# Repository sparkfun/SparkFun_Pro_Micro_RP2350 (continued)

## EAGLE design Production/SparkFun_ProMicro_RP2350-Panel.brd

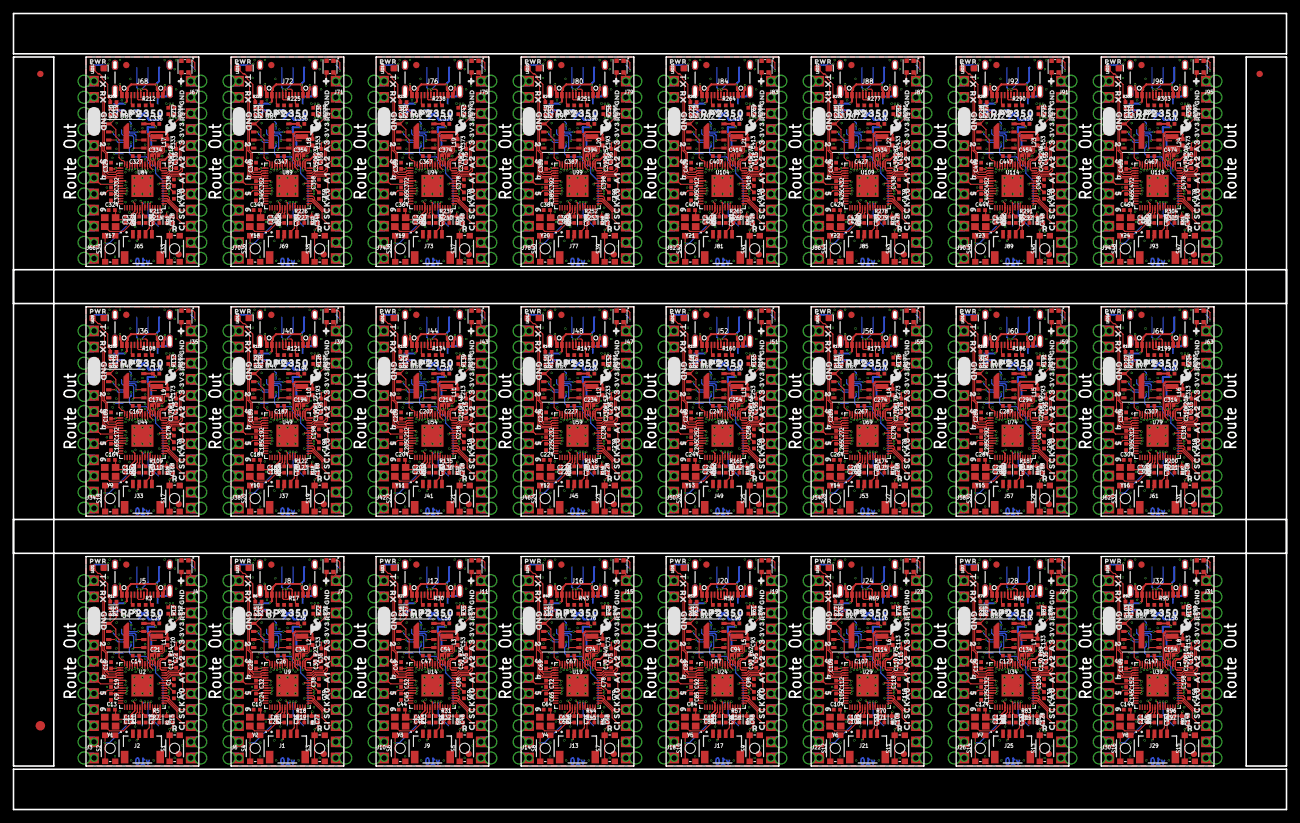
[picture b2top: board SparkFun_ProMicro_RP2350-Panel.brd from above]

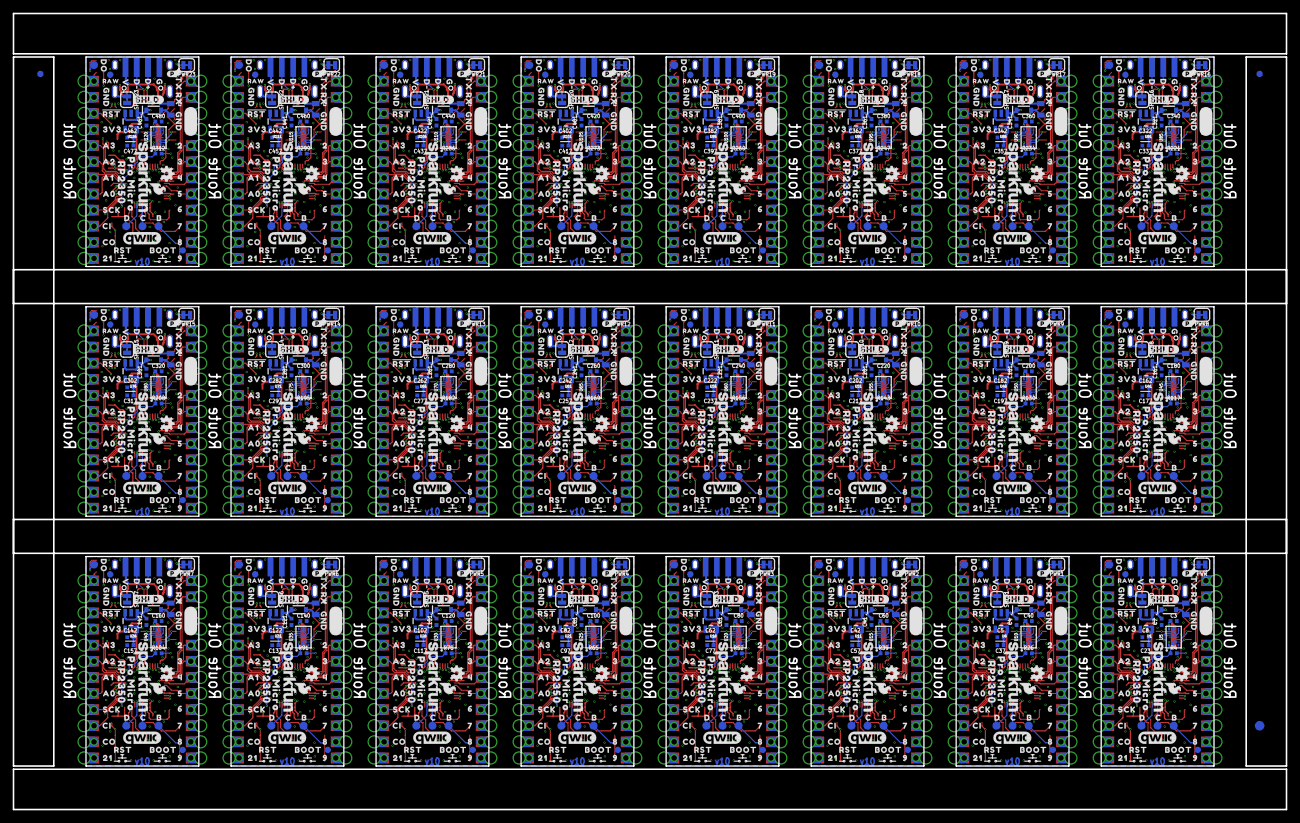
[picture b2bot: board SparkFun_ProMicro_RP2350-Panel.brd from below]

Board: 4 copper layers, 200.7 x 125.5 mm, 2934 parts (1395 on the bottom side), 1272 nets.

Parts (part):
C1, C2, C3, C9, C12, C14, C15, C16, C17, C18, C19, C24, C25, C26, C27, C28, C29, C30, C31, C32, C36, C38, C39, C40, C45, C46, C47, C48, C49, C50, C51, C52, C56, C58, C59, C60, C65, C66, C67, C68, C69, C70, C71, C72, C76, C78, C79, C80, C85, C86, C87, C88, C89, C90, C91, C92, C96, C98, C99, C100, C105, C106, C107, C108, C109, C110, C111, C112, C116, C118, C119, C120, C125, C126, C127, C128, C129, C130, C131, C132, C136, C138, C139, C140, C145, C146, C147, C148, C149, C150, C151, C152, C156, C158, C159, C160, C165, C166, C167, C168, C169, C170, C171, C172, C176, C178, C179, C180, C185, C186, C187, C188, C189, C190, C191, C192, C196, C198, C199, C200, C205, C206, C207, C208, C209, C210, C211, C212, C216, C218, C219, C220, C225, C226, C227, C228, C229, C230, C231, C232, C236, C238, C239, C240, C245, C246, C247, C248, C249, C250, C251, C252, C256, C258, C259, C260, C265, C266, C267, C268, C269, C270, C271, C272, C276, C278, C279, C280, C285, C286, C287, C288, C289, C290, C291, C292, C296, C298, C299, C300, C305, C306, C307, C308, C309, C310, C311, C312, C316, C318, C319, C320, C325, C326, C327, C328, C329, C330, C331, C332, C336, C338, C339, C340, C345, C346, C347, C348, C349, C350, C351, C352, C356, C358, C359, C360, C365, C366, C367, C368, C369, C370, C371, C372, C376, C378, C379, C380, C385, C386, C387, C388, C389, C390, C391, C392, C396, C398, C399, C400, C405, C406, C407, C408, C409, C410, C411, C412, C416, C418, C419, C420, C425, C426, C427, C428, C429, C430, C431, C432, C436, C438, C439, C440, C445, C446, C447, C448, C449, C450, C451, C452, C456, C458, C459, C460, C465, C466, C467, C468, C469, C470, C471, C472, C476, C478, C479, C480: 0.1uF; 0402-TIGHT
C4, C5, C7, C8, C20, C21, C33, C34, C41, C42, C53, C54, C61, C62, C73, C74, C81, C82, C93, C94, C101, C102, C113, C114, C121, C122, C133, C134, C141, C142, C153, C154, C161, C162, C173, C174, C181, C182, C193, C194, C201, C202, C213, C214, C221, C222, C233, C234, C241, C242, C253, C254, C261, C262, C273, C274, C281, C282, C293, C294, C301, C302, C313, C314, C321, C322, C333, C334, C341, C342, C353, C354, C361, C362, C373, C374, C381, C382, C393, C394, C401, C402, C413, C414, C421, C422, C433, C434, C441, C442, C453, C454, C461, C462, C473, C474: 10uF; 0402-TIGHT
C6, C10, C11, C13, C43, C44, C63, C64, C83, C84, C103, C104, C123, C124, C143, C144, C163, C164, C183, C184, C203, C204, C223, C224, C243, C244, C263, C264, C283, C284, C303, C304, C323, C324, C343, C344, C363, C364, C383, C384, C403, C404, C423, C424, C443, C444, C463, C464: 15pF; 0402-TIGHT
C22, C23, C35, C37, C55, C57, C75, C77, C95, C97, C115, C117, C135, C137, C155, C157, C175, C177, C195, C197, C215, C217, C235, C237, C255, C257, C275, C277, C295, C297, C315, C317, C335, C337, C355, C357, C375, C377, C395, C397, C415, C417, C435, C437, C455, C457, C475, C477: 2.2uF; 0402-TIGHT
D1, D2, D3, D4, D5, D6, D7, D8, D9, D10, D11, D12, D13, D14, D15, D16, D17, D18, D19, D20, D21, D22, D23, D24: 3A/10V/280mV; SOD-323
E$1, E$2, E$3, E$4: FIDUCIAL-1X2
E$5, E$6: FIDUCIAL-1.5X3
F1, F2, F3, F4, F5, F6, F7, F8, F9, F10, F11, F12, F13, F14, F15, F16, F17, F18, F19, F20, F21, F22, F23, F24: 6V 0.5A; 0805
J1, J2, J9, J13, J17, J21, J25, J29, J33, J37, J41, J45, J49, J53, J57, J61, J65, J69, J73, J77, J81, J85, J89, J93: QWIIC_RIGHT_ANGLE; JST04_1MM_RA
J3, J4, J6, J7, J10, J11, J14, J15, J18, J19, J22, J23, J26, J27, J30, J31, J34, J35, J38, J39, J42, J43, J46, J47, J50, J51, J54, J55, J58, J59, J62, J63, J66, J67, J70, J71, J74, J75, J78, J79, J82, J83, J86, J87, J90, J91, J94, J95: 1X12_CASTELLATED
J5, J8, J12, J16, J20, J24, J28, J32, J36, J40, J44, J48, J52, J56, J60, J64, J68, J72, J76, J80, J84, J88, J92, J96: USB Female Type C Connector; USB-C-16P_4LAYER-PADS
JP1, JP2, JP3, JP4, JP5, JP6, JP8, JP9, JP10, JP11, JP13, JP15, JP16, JP17, JP19, JP20, JP21, JP22, JP24, JP25, JP26, JP27, JP29, JP30, JP31, JP32, JP34, JP35, JP36, JP37, JP39, JP40, JP41, JP42, JP44, JP45, JP46, JP47, JP49, JP50, JP51, JP52, JP54, JP55, JP56, JP57, JP59, JP60, JP61, JP62, JP64, JP65, JP66, JP67, JP69, JP70, JP71, JP72, JP74, JP75, JP76, JP77, JP79, JP80, JP81, JP82, JP84, JP85, JP86, JP87, JP89, JP90, JP91, JP92, JP94, JP95, JP96, JP97, JP99, JP100, JP101, JP102, JP104, JP105, JP106, JP107, JP109, JP110, JP111, JP112, JP114, JP115, JP116, JP117, JP119, JP120: FIDUCIAL1X2; FIDUCIAL-1X2
JP7, JP12, JP14, JP18, JP23, JP28, JP33, JP38, JP43, JP48, JP53, JP58, JP63, JP68, JP73, JP78, JP83, JP88, JP93, JP98, JP103, JP108, JP113, JP118: USB_SOLDER_PADS; USB-SOLDER-PADS
L1, L2, L3, L4, L5, L6, L7, L8, L9, L10, L11, L12, L13, L14, L15, L16, L17, L18, L19, L20, L21, L22, L23, L24: 4.7μH; 1008(2520)
LED1, LED2, LED3, LED4, LED5, LED6, LED7, LED8, LED9, LED10, LED11, LED12, LED13, LED14, LED15, LED16, LED17, LED18, LED19, LED20, LED21, LED22, LED23, LED24: Red; LED-0603
LOGO1, LOGO2, LOGO7, LOGO10, LOGO13, LOGO16, LOGO19, LOGO22, LOGO25, LOGO28, LOGO31, LOGO34, LOGO37, LOGO40, LOGO43, LOGO46, LOGO49, LOGO52, LOGO55, LOGO58, LOGO61, LOGO64, LOGO67, LOGO70: SFE_LOGO_NAME_FLAME.1_INCH; SFE_LOGO_NAME_FLAME_.1
LOGO3, LOGO5, LOGO8, LOGO11, LOGO14, LOGO17, LOGO20, LOGO23, LOGO26, LOGO29, LOGO32, LOGO35, LOGO38, LOGO41, LOGO44, LOGO47, LOGO50, LOGO53, LOGO56, LOGO59, LOGO62, LOGO65, LOGO68, LOGO71: QWIIC_LOGO_6MM; QWIIC_6MM
LOGO4, LOGO6, LOGO9, LOGO12, LOGO15, LOGO18, LOGO21, LOGO24, LOGO27, LOGO30, LOGO33, LOGO36, LOGO39, LOGO42, LOGO45, LOGO48, LOGO51, LOGO54, LOGO57, LOGO60, LOGO63, LOGO66, LOGO69, LOGO72: SFE_LOGO_FLAME.1_INCH; SFE_LOGO_FLAME_.1
PWR, PWR1, PWR2, PWR3, PWR4, PWR5, PWR6, PWR7, PWR8, PWR9, PWR10, PWR11, PWR12, PWR13, PWR14, PWR15, PWR16, PWR17, PWR18, PWR19, PWR20, PWR21, PWR22, PWR23: JUMPER-SMT_2_NC_TRACE_SILK; SMT-JUMPER_2_NC_TRACE_SILK
R1, R3, R9, R17, R29, R30, R42, R43, R55, R56, R68, R69, R81, R82, R94, R95, R107, R108, R120, R121, R133, R134, R146, R147, R159, R160, R172, R173, R185, R186, R198, R199, R211, R212, R224, R225, R237, R238, R250, R251, R263, R264, R276, R277, R289, R290, R302, R303: 5.1k; 0402-TIGHT
R2, R4, R8, R16, R25, R26, R28, R38, R39, R41, R51, R52, R54, R64, R65, R67, R77, R78, R80, R90, R91, R93, R103, R104, R106, R116, R117, R119, R129, R130, R132, R142, R143, R145, R155, R156, R158, R168, R169, R171, R181, R182, R184, R194, R195, R197, R207, R208, R210, R220, R221, R223, R233, R234, R236, R246, R247, R249, R259, R260, R262, R272, R273, R275, R285, R286, R288, R298, R299, R301, R311, R312: 10k; 0402-TIGHT
R5, R7, R18, R19, R31, R32, R44, R45, R57, R58, R70, R71, R83, R84, R96, R97, R109, R110, R122, R123, R135, R136, R148, R149, R161, R162, R174, R175, R187, R188, R200, R201, R213, R214, R226, R227, R239, R240, R252, R253, R265, R266, R278, R279, R291, R292, R304, R305: 2.2k; 0402-TIGHT
R6, R11, R27, R40, R53, R66, R79, R92, R105, R118, R131, R144, R157, R170, R183, R196, R209, R222, R235, R248, R261, R274, R287, R300: 4.7k; 0402-TIGHT
R10, R15, R20, R24, R33, R37, R46, R50, R59, R63, R72, R76, R85, R89, R98, R102, R111, R115, R124, R128, R137, R141, R150, R154, R163, R167, R176, R180, R189, R193, R202, R206, R215, R219, R228, R232, R241, R245, R254, R258, R267, R271, R280, R284, R293, R297, R306, R310: 1k; 0402-TIGHT
R12, R13, R21, R22, R34, R35, R47, R48, R60, R61, R73, R74, R86, R87, R99, R100, R112, R113, R125, R126, R138, R139, R151, R152, R164, R165, R177, R178, R190, R191, R203, R204, R216, R217, R229, R230, R242, R243, R255, R256, R268, R269, R281, R282, R294, R295, R307, R308: 27; 0402-TIGHT
R14, R23, R36, R49, R62, R75, R88, R101, R114, R127, R140, R153, R166, R179, R192, R205, R218, R231, R244, R257, R270, R283, R296, R309: 10Ω; 0402-TIGHT
S1, S3, S5, S7, S9, S11, S13, S15, S17, S19, S21, S23, S25, S27, S29, S31, S33, S35, S37, S39, S41, S43, S45, S47: Reset; TACTILE_SWITCH_SMD_4.6X2.8MM
S2, S4, S6, S8, S10, S12, S14, S16, S18, S20, S22, S24, S26, S28, S30, S32, S34, S36, S38, S40, S42, S44, S46, S48: Boot; TACTILE_SWITCH_SMD_4.6X2.8MM
SHLD, SHLD1, SHLD2, SHLD3, SHLD4, SHLD5, SHLD6, SHLD7, SHLD8, SHLD9, SHLD10, SHLD11, SHLD12, SHLD13, SHLD14, SHLD15, SHLD16, SHLD17, SHLD18, SHLD19, SHLD20, SHLD21, SHLD22, SHLD23: JUMPER-SMT_2_NC_TRACE_SILK; SMT-JUMPER_2_NC_TRACE_SILK
TP1, TP2, TP3, TP4, TP5, TP6, TP7, TP8, TP9, TP10, TP11, TP12, TP13, TP14, TP15, TP16, TP17, TP18, TP19, TP20, TP21, TP22, TP23, TP24, TP25, TP26, TP27, TP28, TP29, TP30, TP31, TP32, TP33, TP34, TP35, TP36, TP37, TP38, TP39, TP40, TP41, TP42, TP43, TP44, TP45, TP46, TP47, TP48, TP49, TP50, TP51, TP52, TP53, TP54, TP55, TP56, TP57, TP58, TP59, TP60, TP61, TP62, TP63, TP64, TP65, TP66, TP67, TP68, TP69, TP70, TP71, TP72, TP73, TP74, TP75, TP76, TP77, TP78, TP79, TP80, TP81, TP82, TP83, TP84, TP85, TP86, TP87, TP88, TP89, TP90, TP91, TP92, TP93, TP94, TP95, TP96: TEST-POINT3X5; PAD.03X.05
U1, U6, U11, U16, U21, U26, U31, U36, U41, U46, U51, U56, U61, U66, U71, U76, U81, U86, U91, U96, U101, U106, U111, U116: RT9080-33GJ5; SOT23-5
U2, U9, U14, U19, U24, U29, U34, U39, U44, U49, U54, U59, U64, U69, U74, U79, U84, U89, U94, U99, U104, U109, U114, U119: RP2350A
U3, U8, U13, U18, U23, U28, U33, U38, U43, U48, U53, U58, U63, U68, U73, U78, U83, U88, U93, U98, U103, U108, U113, U118: WS2812_2020; WS2812-2020
U4, U7, U12, U17, U22, U27, U32, U37, U42, U47, U52, U57, U62, U67, U72, U77, U82, U87, U92, U97, U102, U107, U112, U117: W25QXX128MBIT; WSON-8-6X5-SKINNY_CENTERPAD
U5, U10, U15, U20, U25, U30, U35, U40, U45, U50, U55, U60, U65, U70, U75, U80, U85, U90, U95, U100, U105, U110, U115, U120: APS6404L-3SQR-ZR
U$1, U$11, U$47, U$85, U$120, U$144, U$179, U$203, U$238, U$262, U$297, U$321, U$356, U$380, U$415, U$439, U$474, U$498, U$533, U$557, U$592, U$616, U$651, U$675, U$710, U$734, U$769, U$793, U$828, U$852, U$887, U$911, U$946, U$970, U$1005, U$1029, U$1064, U$1088, U$1123, U$1147, U$1182, U$1206, U$1241, U$1265, U$1300, U$1324, U$1359, U$1383: A00
U$2, U$79, U$138, U$197, U$256, U$315, U$374, U$433, U$492, U$551, U$610, U$669, U$728, U$787, U$846, U$905, U$964, U$1023, U$1082, U$1141, U$1200, U$1259, U$1318, U$1377: GND_0
U$3, U$46, U$119, U$178, U$237, U$296, U$355, U$414, U$473, U$532, U$591, U$650, U$709, U$768, U$827, U$886, U$945, U$1004, U$1063, U$1122, U$1181, U$1240, U$1299, U$1358: OSHW-LOGOMINI; OSHW-LOGO-MINI
U$4, U$108, U$167, U$226, U$285, U$344, U$403, U$462, U$521, U$580, U$639, U$698, U$757, U$816, U$875, U$934, U$993, U$1052, U$1111, U$1170, U$1229, U$1288, U$1347, U$1406: PRO_MICRO0
U$5, U$107, U$166, U$225, U$284, U$343, U$402, U$461, U$520, U$579, U$638, U$697, U$756, U$815, U$874, U$933, U$992, U$1051, U$1110, U$1169, U$1228, U$1287, U$1346, U$1405: #0
U$6, U$80, U$139, U$198, U$257, U$316, U$375, U$434, U$493, U$552, U$611, U$670, U$729, U$788, U$847, U$906, U$965, U$1024, U$1083, U$1142, U$1201, U$1260, U$1319, U$1378: 70
U$7, U$81, U$140, U$199, U$258, U$317, U$376, U$435, U$494, U$553, U$612, U$671, U$730, U$789, U$848, U$907, U$966, U$1025, U$1084, U$1143, U$1202, U$1261, U$1320, U$1379: 81
U$8, U$82, U$141, U$200, U$259, U$318, U$377, U$436, U$495, U$554, U$613, U$672, U$731, U$790, U$849, U$908, U$967, U$1026, U$1085, U$1144, U$1203, U$1262, U$1321, U$1380: 92
U$9, U$51, U$64, U$83, U$124, U$142, U$183, U$201, U$242, U$260, U$301, U$319, U$360, U$378, U$419, U$437, U$478, U$496, U$537, U$555, U$596, U$614, U$655, U$673, U$714, U$732, U$773, U$791, U$832, U$850, U$891, U$909, U$950, U$968, U$1009, U$1027, U$1068, U$1086, U$1127, U$1145, U$1186, U$1204, U$1245, U$1263, U$1304, U$1322, U$1363, U$1381: CI4
U$10, U$58, U$67, U$84, U$126, U$143, U$185, U$202, U$244, U$261, U$303, U$320, U$362, U$379, U$421, U$438, U$480, U$497, U$539, U$556, U$598, U$615, U$657, U$674, U$716, U$733, U$775, U$792, U$834, U$851, U$893, U$910, U$952, U$969, U$1011, U$1028, U$1070, U$1087, U$1129, U$1146, U$1188, U$1205, U$1247, U$1264, U$1306, U$1323, U$1365, U$1382: SCK3
U$12, U$20, U$48, U$86, U$121, U$145, U$180, U$204, U$239, U$263, U$298, U$322, U$357, U$381, U$416, U$440, U$475, U$499, U$534, U$558, U$593, U$617, U$652, U$676, U$711, U$735, U$770, U$794, U$829, U$853, U$888, U$912, U$947, U$971, U$1006, U$1030, U$1065, U$1089, U$1124, U$1148, U$1183, U$1207, U$1242, U$1266, U$1301, U$1325, U$1360, U$1384: A10
U$13, U$33, U$49, U$87, U$122, U$146, U$181, U$205, U$240, U$264, U$299, U$323, U$358, U$382, U$417, U$441, U$476, U$500, U$535, U$559, U$594, U$618, U$653, U$677, U$712, U$736, U$771, U$795, U$830, U$854, U$889, U$913, U$948, U$972, U$1007, U$1031, U$1066, U$1090, U$1125, U$1149, U$1184, U$1208, U$1243, U$1267, U$1302, U$1326, U$1361, U$1385: A21
U$14, U$39, U$50, U$88, U$123, U$147, U$182, U$206, U$241, U$265, U$300, U$324, U$359, U$383, U$418, U$442, U$477, U$501, U$536, U$560, U$595, U$619, U$654, U$678, U$713, U$737, U$772, U$796, U$831, U$855, U$890, U$914, U$949, U$973, U$1008, U$1032, U$1067, U$1091, U$1126, U$1150, U$1185, U$1209, U$1244, U$1268, U$1303, U$1327, U$1362, U$1386: A32
U$15, U$22, U$72, U$74, U$91, U$104, U$135, U$150, U$163, U$194, U$209, U$222, U$253, U$268, U$281, U$312, U$327, U$340, U$371, U$386, U$399, U$430, U$445, U$458, U$489, U$504, U$517, U$548, U$563, U$576, U$607, U$622, U$635, U$666, U$681, U$694, U$725, U$740, U$753, U$784, U$799, U$812, U$843, U$858, U$871, U$902, U$917, U$930, U$961, U$976, U$989, U$1020, U$1035, U$1048, U$1079, U$1094, U$1107, U$1138, U$1153, U$1166, U$1197, U$1212, U$1225, U$1256, U$1271, U$1284, U$1315, U$1330, U$1343, U$1374, U$1389, U$1402: GND2
U$16, U$103, U$162, U$221, U$280, U$339, U$398, U$457, U$516, U$575, U$634, U$693, U$752, U$811, U$870, U$929, U$988, U$1047, U$1106, U$1165, U$1224, U$1283, U$1342, U$1401: 3V3_0
U$17, U$105, U$164, U$223, U$282, U$341, U$400, U$459, U$518, U$577, U$636, U$695, U$754, U$813, U$872, U$931, U$990, U$1049, U$1108, U$1167, U$1226, U$1285, U$1344, U$1403: RAW0
U$18, U$109, U$168, U$227, U$286, U$345, U$404, U$463, U$522, U$581, U$640, U$699, U$758, U$817, U$876, U$935, U$994, U$1053, U$1112, U$1171, U$1230, U$1289, U$1348, U$1407: C0
U$19, U$76, U$78, U$89, U$137, U$148, U$196, U$207, U$255, U$266, U$314, U$325, U$373, U$384, U$432, U$443, U$491, U$502, U$550, U$561, U$609, U$620, U$668, U$679, U$727, U$738, U$786, U$797, U$845, U$856, U$904, U$915, U$963, U$974, U$1022, U$1033, U$1081, U$1092, U$1140, U$1151, U$1199, U$1210, U$1258, U$1269, U$1317, U$1328, U$1376, U$1387: TX0
U$21, U$75, U$77, U$90, U$136, U$149, U$195, U$208, U$254, U$267, U$313, U$326, U$372, U$385, U$431, U$444, U$490, U$503, U$549, U$562, U$608, U$621, U$667, U$680, U$726, U$739, U$785, U$798, U$844, U$857, U$903, U$916, U$962, U$975, U$1021, U$1034, U$1080, U$1093, U$1139, U$1152, U$1198, U$1211, U$1257, U$1270, U$1316, U$1329, U$1375, U$1388: RX1
U$23, U$53, U$59, U$92, U$127, U$151, U$186, U$210, U$245, U$269, U$304, U$328, U$363, U$387, U$422, U$446, U$481, U$505, U$540, U$564, U$599, U$623, U$658, U$682, U$717, U$741, U$776, U$800, U$835, U$859, U$894, U$918, U$953, U$977, U$1012, U$1036, U$1071, U$1095, U$1130, U$1154, U$1189, U$1213, U$1248, U$1272, U$1307, U$1331, U$1366, U$1390: 20
U$24, U$54, U$60, U$93, U$128, U$152, U$187, U$211, U$246, U$270, U$305, U$329, U$364, U$388, U$423, U$447, U$482, U$506, U$541, U$565, U$600, U$624, U$659, U$683, U$718, U$742, U$777, U$801, U$836, U$860, U$895, U$919, U$954, U$978, U$1013, U$1037, U$1072, U$1096, U$1131, U$1155, U$1190, U$1214, U$1249, U$1273, U$1308, U$1332, U$1367, U$1391: 31
U$25, U$55, U$61, U$94, U$129, U$153, U$188, U$212, U$247, U$271, U$306, U$330, U$365, U$389, U$424, U$448, U$483, U$507, U$542, U$566, U$601, U$625, U$660, U$684, U$719, U$743, U$778, U$802, U$837, U$861, U$896, U$920, U$955, U$979, U$1014, U$1038, U$1073, U$1097, U$1132, U$1156, U$1191, U$1215, U$1250, U$1274, U$1309, U$1333, U$1368, U$1392: 42
U$26, U$56, U$62, U$95, U$130, U$154, U$189, U$213, U$248, U$272, U$307, U$331, U$366, U$390, U$425, U$449, U$484, U$508, U$543, U$567, U$602, U$626, U$661, U$685, U$720, U$744, U$779, U$803, U$838, U$862, U$897, U$921, U$956, U$980, U$1015, U$1039, U$1074, U$1098, U$1133, U$1157, U$1192, U$1216, U$1251, U$1275, U$1310, U$1334, U$1369, U$1393: 53
U$27, U$57, U$63, U$96, U$131, U$155, U$190, U$214, U$249, U$273, U$308, U$332, U$367, U$391, U$426, U$450, U$485, U$509, U$544, U$568, U$603, U$627, U$662, U$686, U$721, U$745, U$780, U$804, U$839, U$863, U$898, U$922, U$957, U$981, U$1016, U$1040, U$1075, U$1099, U$1134, U$1158, U$1193, U$1217, U$1252, U$1276, U$1311, U$1335, U$1370, U$1394: 64
U$28, U$97, U$156, U$215, U$274, U$333, U$392, U$451, U$510, U$569, U$628, U$687, U$746, U$805, U$864, U$923, U$982, U$1041, U$1100, U$1159, U$1218, U$1277, U$1336, U$1395: D#1
U$29, U$98, U$157, U$216, U$275, U$334, U$393, U$452, U$511, U$570, U$629, U$688, U$747, U$806, U$865, U$924, U$983, U$1042, U$1101, U$1160, U$1219, U$1278, U$1337, U$1396: D#2
U$30, U$99, U$158, U$217, U$276, U$335, U$394, U$453, U$512, U$571, U$630, U$689, U$748, U$807, U$866, U$925, U$984, U$1043, U$1102, U$1161, U$1220, U$1279, U$1338, U$1397: G0
U$31, U$100, U$159, U$218, U$277, U$336, U$395, U$454, U$513, U$572, U$631, U$690, U$749, U$808, U$867, U$926, U$985, U$1044, U$1103, U$1162, U$1221, U$1280, U$1339, U$1398: V3
U$32, U$101, U$160, U$219, U$278, U$337, U$396, U$455, U$514, U$573, U$632, U$691, U$750, U$809, U$868, U$927, U$986, U$1045, U$1104, U$1163, U$1222, U$1281, U$1340, U$1399: 210
U$34, U$102, U$161, U$220, U$279, U$338, U$397, U$456, U$515, U$574, U$633, U$692, U$751, U$810, U$869, U$928, U$987, U$1046, U$1105, U$1164, U$1223, U$1282, U$1341, U$1400: #RST#0
U$35, U$110, U$169, U$228, U$287, U$346, U$405, U$464, U$523, U$582, U$641, U$700, U$759, U$818, U$877, U$936, U$995, U$1054, U$1113, U$1172, U$1231, U$1290, U$1349, U$1408: D1
U$36, U$115, U$174, U$233, U$292, U$351, U$410, U$469, U$528, U$587, U$646, U$705, U$764, U$823, U$882, U$941, U$1000, U$1059, U$1118, U$1177, U$1236, U$1295, U$1354, U$1413: #P#0
U$37, U$106, U$165, U$224, U$283, U$342, U$401, U$460, U$519, U$578, U$637, U$696, U$755, U$814, U$873, U$932, U$991, U$1050, U$1109, U$1168, U$1227, U$1286, U$1345, U$1404: R0
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
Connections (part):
0/TX0: J3.12, J3.12B, U2.2
0/TX1: J6.12, J6.12B, U9.2
0/TX2: J10.12, J10.12B, U14.2
0/TX3: J14.12, J14.12B, U19.2
0/TX4: J18.12, J18.12B, U24.2
0/TX5: J22.12, J22.12B, U29.2
0/TX6: J26.12, J26.12B, U34.2
0/TX7: J30.12, J30.12B, U39.2
0/TX8: J34.12, J34.12B, U44.2
0/TX9: J38.12, J38.12B, U49.2
0/TX10: J42.12, J42.12B, U54.2
0/TX11: J46.12, J46.12B, U59.2
0/TX12: J50.12, J50.12B, U64.2
0/TX13: J54.12, J54.12B, U69.2
0/TX14: J58.12, J58.12B, U74.2
0/TX15: J62.12, J62.12B, U79.2
0/TX16: J66.12, J66.12B, U84.2
0/TX17: J70.12, J70.12B, U89.2
0/TX18: J74.12, J74.12B, U94.2
0/TX19: J78.12, J78.12B, U99.2
0/TX20: J82.12, J82.12B, U104.2
0/TX21: J86.12, J86.12B, U109.2
0/TX22: J90.12, J90.12B, U114.2
0/TX23: J94.12, J94.12B, U119.2
1: J6.5, J6.5B, U9.8
1.1V: C1.1, C18.1, C19.1, C20.1, L1.1, U2.6, U2.23, U2.39, U2.50
1.1V1: C31.1, C32.1, C33.1, C38.1, L2.1, U9.6, U9.23, U9.39, U9.50
1.1V2: C51.1, C52.1, C53.1, C58.1, L3.1, U14.6, U14.23, U14.39, U14.50
1.1V3: C71.1, C72.1, C73.1, C78.1, L4.1, U19.6, U19.23, U19.39, U19.50
1.1V4: C91.1, C92.1, C93.1, C98.1, L5.1, U24.6, U24.23, U24.39, U24.50
1.1V5: C111.1, C112.1, C113.1, C118.1, L6.1, U29.6, U29.23, U29.39, U29.50
1.1V6: C131.1, C132.1, C133.1, C138.1, L7.1, U34.6, U34.23, U34.39, U34.50
1.1V7: C151.1, C152.1, C153.1, C158.1, L8.1, U39.6, U39.23, U39.39, U39.50
1.1V8: C171.1, C172.1, C173.1, C178.1, L9.1, U44.6, U44.23, U44.39, U44.50
1.1V9: C191.1, C192.1, C193.1, C198.1, L10.1, U49.6, U49.23, U49.39, U49.50
1.1V10: C211.1, C212.1, C213.1, C218.1, L11.1, U54.6, U54.23, U54.39, U54.50
1.1V11: C231.1, C232.1, C233.1, C238.1, L12.1, U59.6, U59.23, U59.39, U59.50
1.1V12: C251.1, C252.1, C253.1, C258.1, L13.1, U64.6, U64.23, U64.39, U64.50
1.1V13: C271.1, C272.1, C273.1, C278.1, L14.1, U69.6, U69.23, U69.39, U69.50
1.1V14: C291.1, C292.1, C293.1, C298.1, L15.1, U74.6, U74.23, U74.39, U74.50
1.1V15: C311.1, C312.1, C313.1, C318.1, L16.1, U79.6, U79.23, U79.39, U79.50
1.1V16: C331.1, C332.1, C333.1, C338.1, L17.1, U84.6, U84.23, U84.39, U84.50
1.1V17: C351.1, C352.1, C353.1, C358.1, L18.1, U89.6, U89.23, U89.39, U89.50
1.1V18: C371.1, C372.1, C373.1, C378.1, L19.1, U94.6, U94.23, U94.39, U94.50
1.1V19: C391.1, C392.1, C393.1, C398.1, L20.1, U99.6, U99.23, U99.39, U99.50
1.1V20: C411.1, C412.1, C413.1, C418.1, L21.1, U104.6, U104.23, U104.39, U104.50
1.1V21: C431.1, C432.1, C433.1, C438.1, L22.1, U109.6, U109.23, U109.39, U109.50
1.1V22: C451.1, C452.1, C453.1, C458.1, L23.1, U114.6, U114.23, U114.39, U114.50
1.1V23: C471.1, C472.1, C473.1, C478.1, L24.1, U119.6, U119.23, U119.39, U119.50
1/RX0: J3.11, J3.11B, U2.3
1/RX1: J6.11, J6.11B, U9.3
1/RX2: J10.11, J10.11B, U14.3
1/RX3: J14.11, J14.11B, U19.3
1/RX4: J18.11, J18.11B, U24.3
1/RX5: J22.11, J22.11B, U29.3
1/RX6: J26.11, J26.11B, U34.3
1/RX7: J30.11, J30.11B, U39.3
1/RX8: J34.11, J34.11B, U44.3
1/RX9: J38.11, J38.11B, U49.3
1/RX10: J42.11, J42.11B, U54.3
1/RX11: J46.11, J46.11B, U59.3
1/RX12: J50.11, J50.11B, U64.3
1/RX13: J54.11, J54.11B, U69.3
1/RX14: J58.11, J58.11B, U74.3
1/RX15: J62.11, J62.11B, U79.3
1/RX16: J66.11, J66.11B, U84.3
1/RX17: J70.11, J70.11B, U89.3
1/RX18: J74.11, J74.11B, U94.3
1/RX19: J78.11, J78.11B, U99.3
1/RX20: J82.11, J82.11B, U104.3
1/RX21: J86.11, J86.11B, U109.3
1/RX22: J90.11, J90.11B, U114.3
1/RX23: J94.11, J94.11B, U119.3
2: J3.8, J3.8B, U2.4
3: J3.7, J3.7B, U2.5
3.3V: C2.1, C3.1, C8.2, C9.1, C12.1, C14.1, C15.1, C16.1, C17.1, C21.1, C23.1, C29.1, J2.2, J4.4, J4.4B, R2.2, R4.2, R5.2, R7.2, R11.2, R14.2, R16.2, U1.5, U2.1, U2.11, U2.20, U2.30, U2.38, U2.45, U2.49, U2.53, U2.54, U4.8, U5.8
3.3V1: C5.2, C24.1, C25.1, C26.1, C27.1, C28.1, C30.1, C34.1, C36.1, C37.1, C39.1, C40.1, J1.2, J7.4, J7.4B, R6.2, R8.2, R18.2, R19.2, R23.2, R25.2, R26.2, U6.5, U7.8, U9.1, U9.11, U9.20, U9.30, U9.38, U9.45, U9.49, U9.53, U9.54, U10.8
3.3V2: C42.2, C45.1, C46.1, C47.1, C48.1, C49.1, C50.1, C54.1, C56.1, C57.1, C59.1, C60.1, J9.2, J11.4, J11.4B, R27.2, R28.2, R31.2, R32.2, R36.2, R38.2, R39.2, U11.5, U12.8, U14.1, U14.11, U14.20, U14.30, U14.38, U14.45, U14.49, U14.53, U14.54, U15.8
3.3V3: C62.2, C65.1, C66.1, C67.1, C68.1, C69.1, C70.1, C74.1, C76.1, C77.1, C79.1, C80.1, J13.2, J15.4, J15.4B, R40.2, R41.2, R44.2, R45.2, R49.2, R51.2, R52.2, U16.5, U17.8, U19.1, U19.11, U19.20, U19.30, U19.38, U19.45, U19.49, U19.53, U19.54, U20.8
3.3V4: C82.2, C85.1, C86.1, C87.1, C88.1, C89.1, C90.1, C94.1, C96.1, C97.1, C99.1, C100.1, J17.2, J19.4, J19.4B, R53.2, R54.2, R57.2, R58.2, R62.2, R64.2, R65.2, U21.5, U22.8, U24.1, U24.11, U24.20, U24.30, U24.38, U24.45, U24.49, U24.53, U24.54, U25.8
3.3V5: C102.2, C105.1, C106.1, C107.1, C108.1, C109.1, C110.1, C114.1, C116.1, C117.1, C119.1, C120.1, J21.2, J23.4, J23.4B, R66.2, R67.2, R70.2, R71.2, R75.2, R77.2, R78.2, U26.5, U27.8, U29.1, U29.11, U29.20, U29.30, U29.38, U29.45, U29.49, U29.53, U29.54, U30.8
3.3V6: C122.2, C125.1, C126.1, C127.1, C128.1, C129.1, C130.1, C134.1, C136.1, C137.1, C139.1, C140.1, J25.2, J27.4, J27.4B, R79.2, R80.2, R83.2, R84.2, R88.2, R90.2, R91.2, U31.5, U32.8, U34.1, U34.11, U34.20, U34.30, U34.38, U34.45, U34.49, U34.53, U34.54, U35.8
3.3V7: C142.2, C145.1, C146.1, C147.1, C148.1, C149.1, C150.1, C154.1, C156.1, C157.1, C159.1, C160.1, J29.2, J31.4, J31.4B, R92.2, R93.2, R96.2, R97.2, R101.2, R103.2, R104.2, U36.5, U37.8, U39.1, U39.11, U39.20, U39.30, U39.38, U39.45, U39.49, U39.53, U39.54, U40.8
3.3V8: C162.2, C165.1, C166.1, C167.1, C168.1, C169.1, C170.1, C174.1, C176.1, C177.1, C179.1, C180.1, J33.2, J35.4, J35.4B, R105.2, R106.2, R109.2, R110.2, R114.2, R116.2, R117.2, U41.5, U42.8, U44.1, U44.11, U44.20, U44.30, U44.38, U44.45, U44.49, U44.53, U44.54, U45.8
3.3V9: C182.2, C185.1, C186.1, C187.1, C188.1, C189.1, C190.1, C194.1, C196.1, C197.1, C199.1, C200.1, J37.2, J39.4, J39.4B, R118.2, R119.2, R122.2, R123.2, R127.2, R129.2, R130.2, U46.5, U47.8, U49.1, U49.11, U49.20, U49.30, U49.38, U49.45, U49.49, U49.53, U49.54, U50.8
3.3V10: C202.2, C205.1, C206.1, C207.1, C208.1, C209.1, C210.1, C214.1, C216.1, C217.1, C219.1, C220.1, J41.2, J43.4, J43.4B, R131.2, R132.2, R135.2, R136.2, R140.2, R142.2, R143.2, U51.5, U52.8, U54.1, U54.11, U54.20, U54.30, U54.38, U54.45, U54.49, U54.53, U54.54, U55.8
3.3V11: C222.2, C225.1, C226.1, C227.1, C228.1, C229.1, C230.1, C234.1, C236.1, C237.1, C239.1, C240.1, J45.2, J47.4, J47.4B, R144.2, R145.2, R148.2, R149.2, R153.2, R155.2, R156.2, U56.5, U57.8, U59.1, U59.11, U59.20, U59.30, U59.38, U59.45, U59.49, U59.53, U59.54, U60.8
3.3V12: C242.2, C245.1, C246.1, C247.1, C248.1, C249.1, C250.1, C254.1, C256.1, C257.1, C259.1, C260.1, J49.2, J51.4, J51.4B, R157.2, R158.2, R161.2, R162.2, R166.2, R168.2, R169.2, U61.5, U62.8, U64.1, U64.11, U64.20, U64.30, U64.38, U64.45, U64.49, U64.53, U64.54, U65.8
3.3V13: C262.2, C265.1, C266.1, C267.1, C268.1, C269.1, C270.1, C274.1, C276.1, C277.1, C279.1, C280.1, J53.2, J55.4, J55.4B, R170.2, R171.2, R174.2, R175.2, R179.2, R181.2, R182.2, U66.5, U67.8, U69.1, U69.11, U69.20, U69.30, U69.38, U69.45, U69.49, U69.53, U69.54, U70.8
3.3V14: C282.2, C285.1, C286.1, C287.1, C288.1, C289.1, C290.1, C294.1, C296.1, C297.1, C299.1, C300.1, J57.2, J59.4, J59.4B, R183.2, R184.2, R187.2, R188.2, R192.2, R194.2, R195.2, U71.5, U72.8, U74.1, U74.11, U74.20, U74.30, U74.38, U74.45, U74.49, U74.53, U74.54, U75.8
3.3V15: C302.2, C305.1, C306.1, C307.1, C308.1, C309.1, C310.1, C314.1, C316.1, C317.1, C319.1, C320.1, J61.2, J63.4, J63.4B, R196.2, R197.2, R200.2, R201.2, R205.2, R207.2, R208.2, U76.5, U77.8, U79.1, U79.11, U79.20, U79.30, U79.38, U79.45, U79.49, U79.53, U79.54, U80.8
3.3V16: C322.2, C325.1, C326.1, C327.1, C328.1, C329.1, C330.1, C334.1, C336.1, C337.1, C339.1, C340.1, J65.2, J67.4, J67.4B, R209.2, R210.2, R213.2, R214.2, R218.2, R220.2, R221.2, U81.5, U82.8, U84.1, U84.11, U84.20, U84.30, U84.38, U84.45, U84.49, U84.53, U84.54, U85.8
3.3V17: C342.2, C345.1, C346.1, C347.1, C348.1, C349.1, C350.1, C354.1, C356.1, C357.1, C359.1, C360.1, J69.2, J71.4, J71.4B, R222.2, R223.2, R226.2, R227.2, R231.2, R233.2, R234.2, U86.5, U87.8, U89.1, U89.11, U89.20, U89.30, U89.38, U89.45, U89.49, U89.53, U89.54, U90.8
3.3V18: C362.2, C365.1, C366.1, C367.1, C368.1, C369.1, C370.1, C374.1, C376.1, C377.1, C379.1, C380.1, J73.2, J75.4, J75.4B, R235.2, R236.2, R239.2, R240.2, R244.2, R246.2, R247.2, U91.5, U92.8, U94.1, U94.11, U94.20, U94.30, U94.38, U94.45, U94.49, U94.53, U94.54, U95.8
3.3V19: C382.2, C385.1, C386.1, C387.1, C388.1, C389.1, C390.1, C394.1, C396.1, C397.1, C399.1, C400.1, J77.2, J79.4, J79.4B, R248.2, R249.2, R252.2, R253.2, R257.2, R259.2, R260.2, U96.5, U97.8, U99.1, U99.11, U99.20, U99.30, U99.38, U99.45, U99.49, U99.53, U99.54, U100.8
3.3V20: C402.2, C405.1, C406.1, C407.1, C408.1, C409.1, C410.1, C414.1, C416.1, C417.1, C419.1, C420.1, J81.2, J83.4, J83.4B, R261.2, R262.2, R265.2, R266.2, R270.2, R272.2, R273.2, U101.5, U102.8, U104.1, U104.11, U104.20, U104.30, U104.38, U104.45, U104.49, U104.53, U104.54, U105.8
3.3V21: C422.2, C425.1, C426.1, C427.1, C428.1, C429.1, C430.1, C434.1, C436.1, C437.1, C439.1, C440.1, J85.2, J87.4, J87.4B, R274.2, R275.2, R278.2, R279.2, R283.2, R285.2, R286.2, U106.5, U107.8, U109.1, U109.11, U109.20, U109.30, U109.38, U109.45, U109.49, U109.53, U109.54, U110.8
3.3V22: C442.2, C445.1, C446.1, C447.1, C448.1, C449.1, C450.1, C454.1, C456.1, C457.1, C459.1, C460.1, J89.2, J91.4, J91.4B, R287.2, R288.2, R291.2, R292.2, R296.2, R298.2, R299.2, U111.5, U112.8, U114.1, U114.11, U114.20, U114.30, U114.38, U114.45, U114.49, U114.53, U114.54, U115.8
3.3V23: C462.2, C465.1, C466.1, C467.1, C468.1, C469.1, C470.1, C474.1, C476.1, C477.1, C479.1, C480.1, J93.2, J95.4, J95.4B, R300.2, R301.2, R304.2, R305.2, R309.2, R311.2, R312.2, U116.5, U117.8, U119.1, U119.11, U119.20, U119.30, U119.38, U119.45, U119.49, U119.53, U119.54, U120.8
4: J3.6, J3.6B, U2.7
5: J3.5, J3.5B, U2.8
6: J3.4, J3.4B, U2.9
7: J3.3, J3.3B, U2.10
8: J6.6, J6.6B, U9.7
8/TX1: J3.2, J3.2B, U2.12
8/TX2: J6.2, J6.2B, U9.12
8/TX3: J10.2, J10.2B, U14.12
8/TX4: J14.2, J14.2B, U19.12
8/TX5: J18.2, J18.2B, U24.12
8/TX6: J22.2, J22.2B, U29.12
8/TX7: J26.2, J26.2B, U34.12
8/TX8: J30.2, J30.2B, U39.12
8/TX9: J34.2, J34.2B, U44.12
8/TX10: J38.2, J38.2B, U49.12
8/TX11: J42.2, J42.2B, U54.12
8/TX12: J46.2, J46.2B, U59.12
8/TX13: J50.2, J50.2B, U64.12
8/TX14: J54.2, J54.2B, U69.12
8/TX15: J58.2, J58.2B, U74.12
8/TX16: J62.2, J62.2B, U79.12
8/TX17: J66.2, J66.2B, U84.12
8/TX18: J70.2, J70.2B, U89.12
8/TX19: J74.2, J74.2B, U94.12
8/TX20: J78.2, J78.2B, U99.12
8/TX21: J82.2, J82.2B, U104.12
8/TX22: J86.2, J86.2B, U109.12
8/TX23: J90.2, J90.2B, U114.12
8/TX24: J94.2, J94.2B, U119.12
9: J6.4, J6.4B, U9.9
9/RX1: J3.1, J3.1B, U2.13
9/RX2: J6.1, J6.1B, U9.13
9/RX3: J10.1, J10.1B, U14.13
9/RX4: J14.1, J14.1B, U19.13
9/RX5: J18.1, J18.1B, U24.13
9/RX6: J22.1, J22.1B, U29.13
9/RX7: J26.1, J26.1B, U34.13
9/RX8: J30.1, J30.1B, U39.13
9/RX9: J34.1, J34.1B, U44.13
9/RX10: J38.1, J38.1B, U49.13
9/RX11: J42.1, J42.1B, U54.13
9/RX12: J46.1, J46.1B, U59.13
9/RX13: J50.1, J50.1B, U64.13
9/RX14: J54.1, J54.1B, U69.13
9/RX15: J58.1, J58.1B, U74.13
9/RX16: J62.1, J62.1B, U79.13
9/RX17: J66.1, J66.1B, U84.13
9/RX18: J70.1, J70.1B, U89.13
9/RX19: J74.1, J74.1B, U94.13
9/RX20: J78.1, J78.1B, U99.13
9/RX21: J82.1, J82.1B, U104.13
9/RX22: J86.1, J86.1B, U109.13
9/RX23: J90.1, J90.1B, U114.13
9/RX24: J94.1, J94.1B, U119.13
10: J6.3, J6.3B, U9.10
11: J6.8, J6.8B, U9.4
12: J6.7, J6.7B, U9.5
13: J10.5, J10.5B, U14.8
14: J10.6, J10.6B, U14.7
15: J10.4, J10.4B, U14.9
16: J10.3, J10.3B, U14.10
16/SDA: J2.3, R5.1, U2.27
16/SDA1: J1.3, R18.1, U9.27
16/SDA2: J9.3, R31.1, U14.27
16/SDA3: J13.3, R44.1, U19.27
16/SDA4: J17.3, R57.1, U24.27
16/SDA5: J21.3, R70.1, U29.27
16/SDA6: J25.3, R83.1, U34.27
16/SDA7: J29.3, R96.1, U39.27
16/SDA8: J33.3, R109.1, U44.27
16/SDA9: J37.3, R122.1, U49.27
16/SDA10: J41.3, R135.1, U54.27
16/SDA11: J45.3, R148.1, U59.27
16/SDA12: J49.3, R161.1, U64.27
16/SDA13: J53.3, R174.1, U69.27
16/SDA14: J57.3, R187.1, U74.27
16/SDA15: J61.3, R200.1, U79.27
16/SDA16: J65.3, R213.1, U84.27
16/SDA17: J69.3, R226.1, U89.27
16/SDA18: J73.3, R239.1, U94.27
16/SDA19: J77.3, R252.1, U99.27
16/SDA20: J81.3, R265.1, U104.27
16/SDA21: J85.3, R278.1, U109.27
16/SDA22: J89.3, R291.1, U114.27
16/SDA23: J93.3, R304.1, U119.27
17: J10.8, J10.8B, U14.4
17/SCL: J2.4, R7.1, U2.28
17/SCL1: J1.4, R19.1, U9.28
17/SCL2: J9.4, R32.1, U14.28
17/SCL3: J13.4, R45.1, U19.28
17/SCL4: J17.4, R58.1, U24.28
17/SCL5: J21.4, R71.1, U29.28
17/SCL6: J25.4, R84.1, U34.28
17/SCL7: J29.4, R97.1, U39.28
17/SCL8: J33.4, R110.1, U44.28
17/SCL9: J37.4, R123.1, U49.28
17/SCL10: J41.4, R136.1, U54.28
17/SCL11: J45.4, R149.1, U59.28
17/SCL12: J49.4, R162.1, U64.28
17/SCL13: J53.4, R175.1, U69.28
17/SCL14: J57.4, R188.1, U74.28
17/SCL15: J61.4, R201.1, U79.28
17/SCL16: J65.4, R214.1, U84.28
17/SCL17: J69.4, R227.1, U89.28
17/SCL18: J73.4, R240.1, U94.28
17/SCL19: J77.4, R253.1, U99.28
17/SCL20: J81.4, R266.1, U104.28
17/SCL21: J85.4, R279.1, U109.28
17/SCL22: J89.4, R292.1, U114.28
17/SCL23: J93.4, R305.1, U119.28
18: J10.7, J10.7B, U14.5
19: J14.5, J14.5B, U19.8
20: J14.6, J14.6B, U19.7
20/SPI_POCI: J4.10, J4.10B, U2.32
20/SPI_POCI1: J7.10, J7.10B, U9.32
20/SPI_POCI2: J11.10, J11.10B, U14.32
20/SPI_POCI3: J15.10, J15.10B, U19.32
20/SPI_POCI4: J19.10, J19.10B, U24.32
20/SPI_POCI5: J23.10, J23.10B, U29.32
20/SPI_POCI6: J27.10, J27.10B, U34.32
20/SPI_POCI7: J31.10, J31.10B, U39.32
20/SPI_POCI8: J35.10, J35.10B, U44.32
20/SPI_POCI9: J39.10, J39.10B, U49.32
20/SPI_POCI10: J43.10, J43.10B, U54.32
20/SPI_POCI11: J47.10, J47.10B, U59.32
20/SPI_POCI12: J51.10, J51.10B, U64.32
20/SPI_POCI13: J55.10, J55.10B, U69.32
20/SPI_POCI14: J59.10, J59.10B, U74.32
20/SPI_POCI15: J63.10, J63.10B, U79.32
20/SPI_POCI16: J67.10, J67.10B, U84.32
20/SPI_POCI17: J71.10, J71.10B, U89.32
20/SPI_POCI18: J75.10, J75.10B, U94.32
20/SPI_POCI19: J79.10, J79.10B, U99.32
20/SPI_POCI20: J83.10, J83.10B, U104.32
20/SPI_POCI21: J87.10, J87.10B, U109.32
20/SPI_POCI22: J91.10, J91.10B, U114.32
20/SPI_POCI23: J95.10, J95.10B, U119.32
21: J14.4, J14.4B, U19.9
21/SPI_!CS!: J4.12, J4.12B, U2.33
21/SPI_!CS!1: J7.12, J7.12B, U9.33
21/SPI_!CS!2: J11.12, J11.12B, U14.33
21/SPI_!CS!3: J15.12, J15.12B, U19.33
21/SPI_!CS!4: J19.12, J19.12B, U24.33
21/SPI_!CS!5: J23.12, J23.12B, U29.33
21/SPI_!CS!6: J27.12, J27.12B, U34.33
21/SPI_!CS!7: J31.12, J31.12B, U39.33
21/SPI_!CS!8: J35.12, J35.12B, U44.33
21/SPI_!CS!9: J39.12, J39.12B, U49.33
21/SPI_!CS!10: J43.12, J43.12B, U54.33
21/SPI_!CS!11: J47.12, J47.12B, U59.33
21/SPI_!CS!12: J51.12, J51.12B, U64.33
21/SPI_!CS!13: J55.12, J55.12B, U69.33
21/SPI_!CS!14: J59.12, J59.12B, U74.33
21/SPI_!CS!15: J63.12, J63.12B, U79.33
21/SPI_!CS!16: J67.12, J67.12B, U84.33
21/SPI_!CS!17: J71.12, J71.12B, U89.33
21/SPI_!CS!18: J75.12, J75.12B, U94.33
21/SPI_!CS!19: J79.12, J79.12B, U99.33
21/SPI_!CS!20: J83.12, J83.12B, U104.33
21/SPI_!CS!21: J87.12, J87.12B, U109.33
21/SPI_!CS!22: J91.12, J91.12B, U114.33
21/SPI_!CS!23: J95.12, J95.12B, U119.33
22: J14.3, J14.3B, U19.10
22/SPI_SCK: J4.9, J4.9B, U2.34
22/SPI_SCK1: J7.9, J7.9B, U9.34
22/SPI_SCK2: J11.9, J11.9B, U14.34
22/SPI_SCK3: J15.9, J15.9B, U19.34
22/SPI_SCK4: J19.9, J19.9B, U24.34
22/SPI_SCK5: J23.9, J23.9B, U29.34
22/SPI_SCK6: J27.9, J27.9B, U34.34
22/SPI_SCK7: J31.9, J31.9B, U39.34
22/SPI_SCK8: J35.9, J35.9B, U44.34
22/SPI_SCK9: J39.9, J39.9B, U49.34
22/SPI_SCK10: J43.9, J43.9B, U54.34
22/SPI_SCK11: J47.9, J47.9B, U59.34
22/SPI_SCK12: J51.9, J51.9B, U64.34
22/SPI_SCK13: J55.9, J55.9B, U69.34
22/SPI_SCK14: J59.9, J59.9B, U74.34
22/SPI_SCK15: J63.9, J63.9B, U79.34
22/SPI_SCK16: J67.9, J67.9B, U84.34
22/SPI_SCK17: J71.9, J71.9B, U89.34
22/SPI_SCK18: J75.9, J75.9B, U94.34
22/SPI_SCK19: J79.9, J79.9B, U99.34
22/SPI_SCK20: J83.9, J83.9B, U104.34
22/SPI_SCK21: J87.9, J87.9B, U109.34
22/SPI_SCK22: J91.9, J91.9B, U114.34
22/SPI_SCK23: J95.9, J95.9B, U119.34
23: J14.8, J14.8B, U19.4
23/SPI_PICO: J4.11, J4.11B, U2.35
23/SPI_PICO1: J7.11, J7.11B, U9.35
23/SPI_PICO2: J11.11, J11.11B, U14.35
23/SPI_PICO3: J15.11, J15.11B, U19.35
23/SPI_PICO4: J19.11, J19.11B, U24.35
23/SPI_PICO5: J23.11, J23.11B, U29.35
23/SPI_PICO6: J27.11, J27.11B, U34.35
23/SPI_PICO7: J31.11, J31.11B, U39.35
23/SPI_PICO8: J35.11, J35.11B, U44.35
23/SPI_PICO9: J39.11, J39.11B, U49.35
23/SPI_PICO10: J43.11, J43.11B, U54.35
23/SPI_PICO11: J47.11, J47.11B, U59.35
23/SPI_PICO12: J51.11, J51.11B, U64.35
23/SPI_PICO13: J55.11, J55.11B, U69.35
23/SPI_PICO14: J59.11, J59.11B, U74.35
23/SPI_PICO15: J63.11, J63.11B, U79.35
23/SPI_PICO16: J67.11, J67.11B, U84.35
23/SPI_PICO17: J71.11, J71.11B, U89.35
23/SPI_PICO18: J75.11, J75.11B, U94.35
23/SPI_PICO19: J79.11, J79.11B, U99.35
23/SPI_PICO20: J83.11, J83.11B, U104.35
23/SPI_PICO21: J87.11, J87.11B, U109.35
23/SPI_PICO22: J91.11, J91.11B, U114.35
23/SPI_PICO23: J95.11, J95.11B, U119.35
24: J14.7, J14.7B, U19.5
25: J18.5, J18.5B, U24.8
25/WS2812-DI: U2.37, U3.DI
25/WS2812-DI1: U8.DI, U9.37
25/WS2812-DI2: U13.DI, U14.37
25/WS2812-DI3: U18.DI, U19.37
25/WS2812-DI4: U23.DI, U24.37
25/WS2812-DI5: U28.DI, U29.37
25/WS2812-DI6: U33.DI, U34.37
25/WS2812-DI7: U38.DI, U39.37
25/WS2812-DI8: U43.DI, U44.37
25/WS2812-DI9: U48.DI, U49.37
25/WS2812-DI10: U53.DI, U54.37
25/WS2812-DI11: U58.DI, U59.37
25/WS2812-DI12: U63.DI, U64.37
25/WS2812-DI13: U68.DI, U69.37
25/WS2812-DI14: U73.DI, U74.37
25/WS2812-DI15: U78.DI, U79.37
25/WS2812-DI16: U83.DI, U84.37
25/WS2812-DI17: U88.DI, U89.37
25/WS2812-DI18: U93.DI, U94.37
25/WS2812-DI19: U98.DI, U99.37
25/WS2812-DI20: U103.DI, U104.37
25/WS2812-DI21: U108.DI, U109.37
25/WS2812-DI22: U113.DI, U114.37
25/WS2812-DI23: U118.DI, U119.37
26: J18.6, J18.6B, U24.7
27: J18.4, J18.4B, U24.9
28: J18.3, J18.3B, U24.10
29: J18.8, J18.8B, U24.4
30: J18.7, J18.7B, U24.5
31: J22.5, J22.5B, U29.8
32: J22.6, J22.6B, U29.7
33: J22.4, J22.4B, U29.9
34: J22.3, J22.3B, U29.10
35: J22.8, J22.8B, U29.4
36: J22.7, J22.7B, U29.5
37: J26.5, J26.5B, U34.8
38: J26.6, J26.6B, U34.7
39: J26.4, J26.4B, U34.9
40: J26.3, J26.3B, U34.10
41: J26.8, J26.8B, U34.4
42: J26.7, J26.7B, U34.5
43: J30.5, J30.5B, U39.8
44: J30.6, J30.6B, U39.7
45: J30.4, J30.4B, U39.9
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
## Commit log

2024-01-08 Add RP2350A library file
2024-01-08 Add initial design
    Based on ProMicro RP2040 design
2024-01-08 Cleanup
    Rename design files
    Change version number to v01
    Update attributions
    Update silk name
    Update ordering instructions
    Update measures
2024-01-08 Update board thickness
2024-01-08 More cleanup
    Add test point for BOOT net
    Nudge a few traces and vias to improve copper pours
    Approve DRC errors
    Fix traces overlapping vias
    Fix acid traps
2024-01-08 Change C20 and C21 from 2.2uF to 10uF
    Recommended by hardware guidelines
2024-01-09 Design review updates
    Change regulator to RT9080
    Add USB shield jumper and polygon to connect USB shield pads
    Change PWR jumper silk to just be "P" and orient at 90 with silk polygon to connect it
    Remove C6
2024-01-09 Clean up schematic
    Rearrange sections to use whole frame
    Update section titles
    Move power LED and Qwiic connector to their own sections
    Add text to jumpers indicating their functions
    Change power LED to new version and update resistor
    Swap VREG_AVDD and VREG_VIN pins on RP235 symbol to give more space for inductor in schematic
2024-01-09 Update WS2812 symbol
    Use new version so Eagle stops complaining
2024-01-09 Use correct 1.1V power symbol
    Remove dependence on RP2040 library
2024-01-09 Use castellated pad device from SparkFun lib
    Remove dependency of "Castellated" lib
2024-01-09 Add "Castellated Leads" to ordering instructions
2024-01-10 Design review updates
    Change all text and labels in schematic to vector font
    Fix overlapping text with Qwiic connector in schematic
    Add part number to flash memory section title
    Fix acid trap on RAW pad
    Add more GND vias
2024-01-10 DFM adjustments
    Nudge C1 away from C2
    Nudge C20 away from L1
2024-01-10 Improve button silk
    Remove "B" silk label from boot button
    Increase size of "R" silk label for reset button
    Add "BOOT" and "RST" silk to bottom with button symbols
    Move Qwiic logo and test point labels up
2024-01-10 Add v01 production files
2024-01-15 Add PROD_ID for RP2350A
2024-02-26 v10 updates
    Bump version number to v10
    Move bottom pin silk labels away from pads
2024-02-28 Design review updates
    Re-enable layers that accidentally got turned off
    Nudge BOOT and RST silk to be better centered over button art
    Add better silk dot to crystal
2024-02-28 Add v10 production files
2024-03-12 Add PSRAM
2024-03-12 Change version number to v09
2024-03-12 Add v09 panel files
2024-03-12 Add PSRAM datasheet
2024-03-12 Move power components to bottom
    Gives more clearance between components to hopefully improve production yields
2024-03-15 Design review updates
    Change version number to v02 instead of jumping to v09
    Add PROD_ID to PSRAM
    Nudge BOOT trace away from UART trace on adjacent layer
    Fix "2" silk on bottom
    Nudge C13 away from "6" silk on top
    Fix acid trap on pad 5 of U1
2024-03-15 Add v02 panel files
2024-06-04 Bump version number to v10
2024-06-04 Initial docs commit
    Adding GH pages template files in prep for docs content.
2024-06-06 Design review updates
    Rotate BOOT flag to horizontal in schematic
2024-06-06 Remove extra polarity indicator in silkscreen
2024-07-18 Docs update
    Software section update to prep for adding related links for upcoming software additions.
2024-07-23 Photos Upload
    Uploading photos for Hookup Guide.
2024-07-25 Docs Update
    Minor software section updates & adding images to hardware overview.
2024-07-29 Add initial Arducam demo
2024-07-30 Improve Arducam demo synchronization
2024-08-01 Docs update
    Adding assembly photos & updating assembly & software sections for camera demo example.
2024-08-02 Update README.md
    Updating readme.md from template.
2024-08-07 Docs Review Update
    Docs update for release. Adjusting format to separate software sections & final review updates/edits.
2024-08-08 Release update
    Updates for product release. Adding relevant component files & Raspberry Pi links for RP2350.
2024-08-09 Update introduction.md
    Typo fix
2024-08-09 Update micropython_examples.md
    Remove icon
2024-08-13 Minor docs update
    Updating RP2350 features to clarify HSTX support.
2024-08-17 Update README.md
    add link to sparkfun-pico repo in docs section
2024-08-19 Update micropython_examples.md
    Fixing LED example typo.
2024-08-19 Add rainbow UF2 file
    Resolves #3
2024-08-29 Docs software update
    Adding updated MicroPython links and Arduino IDE section
2024-08-29 Deployed 374619b with MkDocs version: 1.6.0
2024-10-25 Update mkdocs.yml
    Analytics update.
2024-10-25 Deployed 80ab194 with MkDocs version: 1.6.1
2024-11-14 Update micropython_setup.md
    Updating to latest MicroPython firmware beta (v04) for the Pro Micro.
2024-12-03 Update micropython_setup.md
    Updating links for latest MicroPython Beta firmware releases.
2024-12-04 Adding CircuitPython
    Adding CircuitPython docs page w/updates to relevant pages.
2024-12-04 Deployed 94a98fa with MkDocs version: 1.6.1
2026-06-03 Deployed 8d3bbac with MkDocs version: 1.6.1
